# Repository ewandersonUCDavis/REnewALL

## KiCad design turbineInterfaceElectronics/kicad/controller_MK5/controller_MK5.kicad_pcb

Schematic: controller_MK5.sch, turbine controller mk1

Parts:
C1, C5, C14: 10uF; C_1206
C2, C6, C7, C8, C11, C12, C13: 1uF; C_0603
C3: 47pF; C_0603
C4: 10uF; C_1210
C9: 0.1u; C_0603
C10: 1u; C_0603
D1, D4, D5, D6, D8, D9, D10: SMAJ30CA‎; D_SMA
D2, D11: B240A-13-F; D_SMA
D3: GREEN; LED_0603_1608Metric_Pad0.82x1.00mm_HandSolder
D7, D12: DB2S31600L; D_SOD-523
F1: 01550900M; littlefuse-omni-blok
J1: 1935161; Phoenix_PT_2POS_5mm
J2, J7, J8, J9: MountingHole-M3; MountingHole_4.3mm_M4
J4, J5: 1935187; Phoenix_PT_4POS_5mm
J6: 1935200; Phoenix_PT_6POS_5mm
Q1, Q2, Q3: BSS138L; SOT-23_NMOSGSD
R1, R2, R3, R4, R10, R11, R12, R13, R14, R15, R21, R22, R23: 1K; R_0603
R5, R6, R7, R16, R17, R18: 1M; R_0603
R8, R29: 10; R_0603
R9, R20: 0R; R_0603
R24, R27: 4.7K; R_0603
U1: 1528-1392-ND; XBEE900HP
U2: OKI-78SR-3.3/1.5-W36-C; OKI-78SR
U3: SN74LV14APWR; TSSOP-14_4.4x5mm_P0.65mm
U4, U5, U6, U8, U9, U10: EL3H7(TA)-VG; EL3H7-G
U7: G6B-2214P-US; omron_relay_P6B_holder
U11: G6B-2114P-US; omron_relay_P6B_holder

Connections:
/EXT_24V: C4.1, F1.2, R9.2, R20.2, U2.1 (VIN)
/EXT_BRAKE: C13.1, D10.A (A1), J6.6, R15.2
/EXT_FAULT1: C6.1, D4.A (A1), J6.1, R2.2
/EXT_FAULT2: C7.1, D5.A (A1), J6.2, R3.2
/EXT_FAULT3: C8.1, D6.A (A1), J6.3, R4.2
/EXT_FAULT4: C11.1, D8.A (A1), J6.4, R13.2
/EXT_PULSE: C12.1, D9.A (A1), J6.5, R14.2
/IN_BRAKE: U1.11 (DIO4/SPI_MOSI), U3.12
/IN_FAULT1: U1.6 (DIO10/PWM0), U3.2
/IN_FAULT2: U1.16 (~RTS~/DIO6), U3.4
/IN_FAULT3: U1.17 (AD3/DIO3/SPI_SS), U3.6
/IN_FAULT4: U1.18 (AD2/DIO2/SPI_CLK), U3.8
/IN_PULSE: U1.19 (AD1/DIO1/SPI_ATTN), U3.10
/OUT_START: R8.1, U1.7 (DIO11/PWM1)
/OUT_STOP: R29.1, U1.4 (DIO12/SPI_MISO)
/START_A1: J5.1, U7.6
/START_A2: J5.2, U7.5
/START_B1: J5.3, U7.3
/START_B2: J5.4, U7.4
/STOP_A1: J4.1, U11.3
/STOP_A2: J4.2, U11.4
/STOP_B1: J4.3, U11.6
/STOP_B2: J4.4, U11.5
/SYS_3V3: C1.1, C2.1, C3.1, C5.1, C9.1, C10.1, C14.1, R1.1, R10.1, R11.1, R12.1, R21.1, R22.1, R23.1, U1.1 (VCC), U2.3 (VOUT), U3.14
/XBEE_ASSO: Q1.G, U1.15 (ASSO/DIO5)
/~XBEE_RST: U1.5 (~RST)
GND: C1.2, C2.2, C3.2, C4.2, C5.2, C6.2, C7.2, C8.2, C9.2, C10.2, C11.2, C12.2, C13.2, C14.2, D1.C (A2), D4.C (A2), D5.C (A2), D6.C (A2), D7.2, D8.C (A2), D9.C (A2), D10.C (A2), D12.2, J1.2, Q1.S, Q2.S, Q3.S, R5.1, R6.1, R7.1, R16.1, R17.1, R18.1, R24.2, R27.2, U1.10 (GND), U2.2 (GND), U3.7, U4.2, U4.3, U5.2, U5.3, U6.2, U6.3, U8.2, U8.3, U9.2, U9.3, U10.2, U10.3
unnamed: D1.A (A1), F1.1, J1.1
unnamed: D2.A, D7.1, Q2.D, U7.1 (-)
unnamed: D2.C, R9.1, U7.8 (+)
unnamed: D3.1, Q1.D
unnamed: D3.2, R1.2
unnamed: D11.A, D12.1, Q3.D, U11.1 (-)
unnamed: D11.C, R20.1, U11.8 (+)
unnamed: Q2.G, R8.2, R24.1
unnamed: Q3.G, R27.1, R29.2
unnamed: R2.1, R5.2, U4.1
unnamed: R3.1, R6.2, U5.1
unnamed: R4.1, R7.2, U6.1
unnamed: R10.2, U3.1, U4.4
unnamed: R11.2, U3.3, U5.4
unnamed: R12.2, U3.5, U6.4
unnamed: R13.1, R16.2, U8.1
unnamed: R14.1, R17.2, U9.1
unnamed: R15.1, R18.2, U10.1
unnamed: R21.2, U3.9, U8.4
unnamed: R22.2, U3.11, U9.4
unnamed: R23.2, U3.13, U10.4

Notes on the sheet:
ISO_REG: NCS3S1203SC OUTPUT RELAY: G6B-2214P-US OUTPUT RELAY: G6B-2114P-US INPUT ISO: EL3H7 HEX INV(w/ schmitt): 74LV14PW,118 TVS: SMAJ30ALFCT-ND connector: 2-pin: 1935161 4-pin: 1935187 6-pin: 1935200
Around 1.6mA
two output parts are in different voltage levels
20mA, 1.2V Vf
INPUT STAGE
OUTPUT STAGE
MAY NEED WATCHDOG HERE
IF NEEDED, REPLACE ALL INV WITH NOT SCHMITT TRIGGER
G6B-2214P-US DC24
3.3V/100 = 33mA

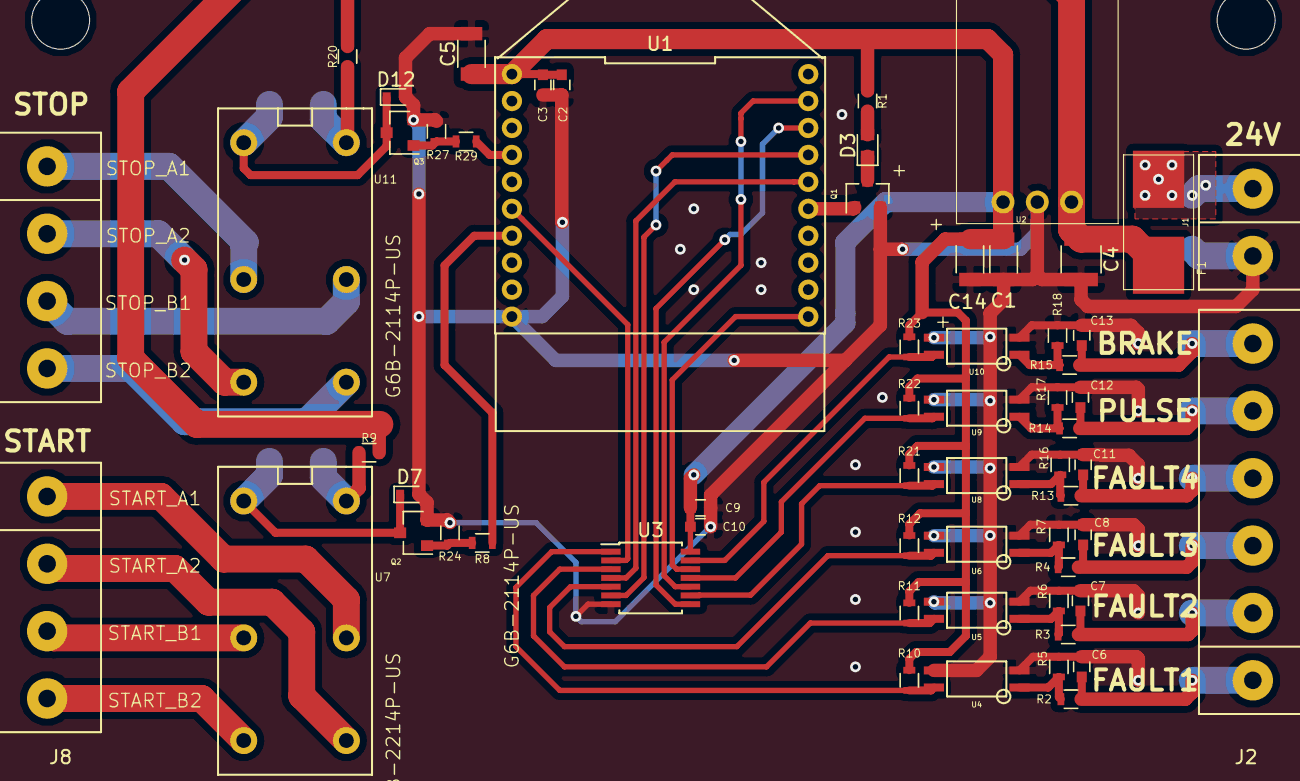
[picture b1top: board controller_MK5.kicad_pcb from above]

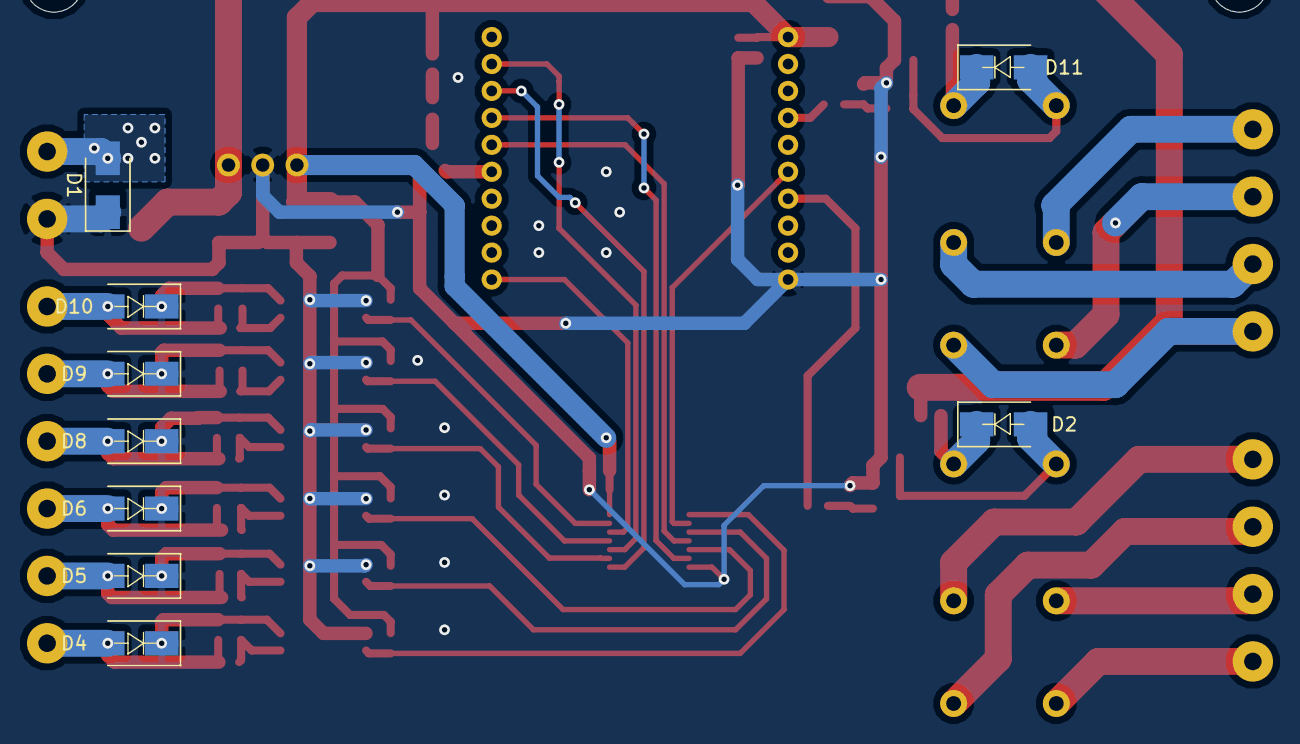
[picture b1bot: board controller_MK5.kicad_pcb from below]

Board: 2 copper layers, 74 parts (9 on the bottom side), 47 nets.

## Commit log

2018-12-19 First Commit
    This commit uploads a variety of required to set up a communication and
    control system like the one described in the REnewALL Wind Turbine
    Communication and Control Report
2019-01-23 Added Negative Price Forecast Scripts
2019-01-23 Removed duplicate file
